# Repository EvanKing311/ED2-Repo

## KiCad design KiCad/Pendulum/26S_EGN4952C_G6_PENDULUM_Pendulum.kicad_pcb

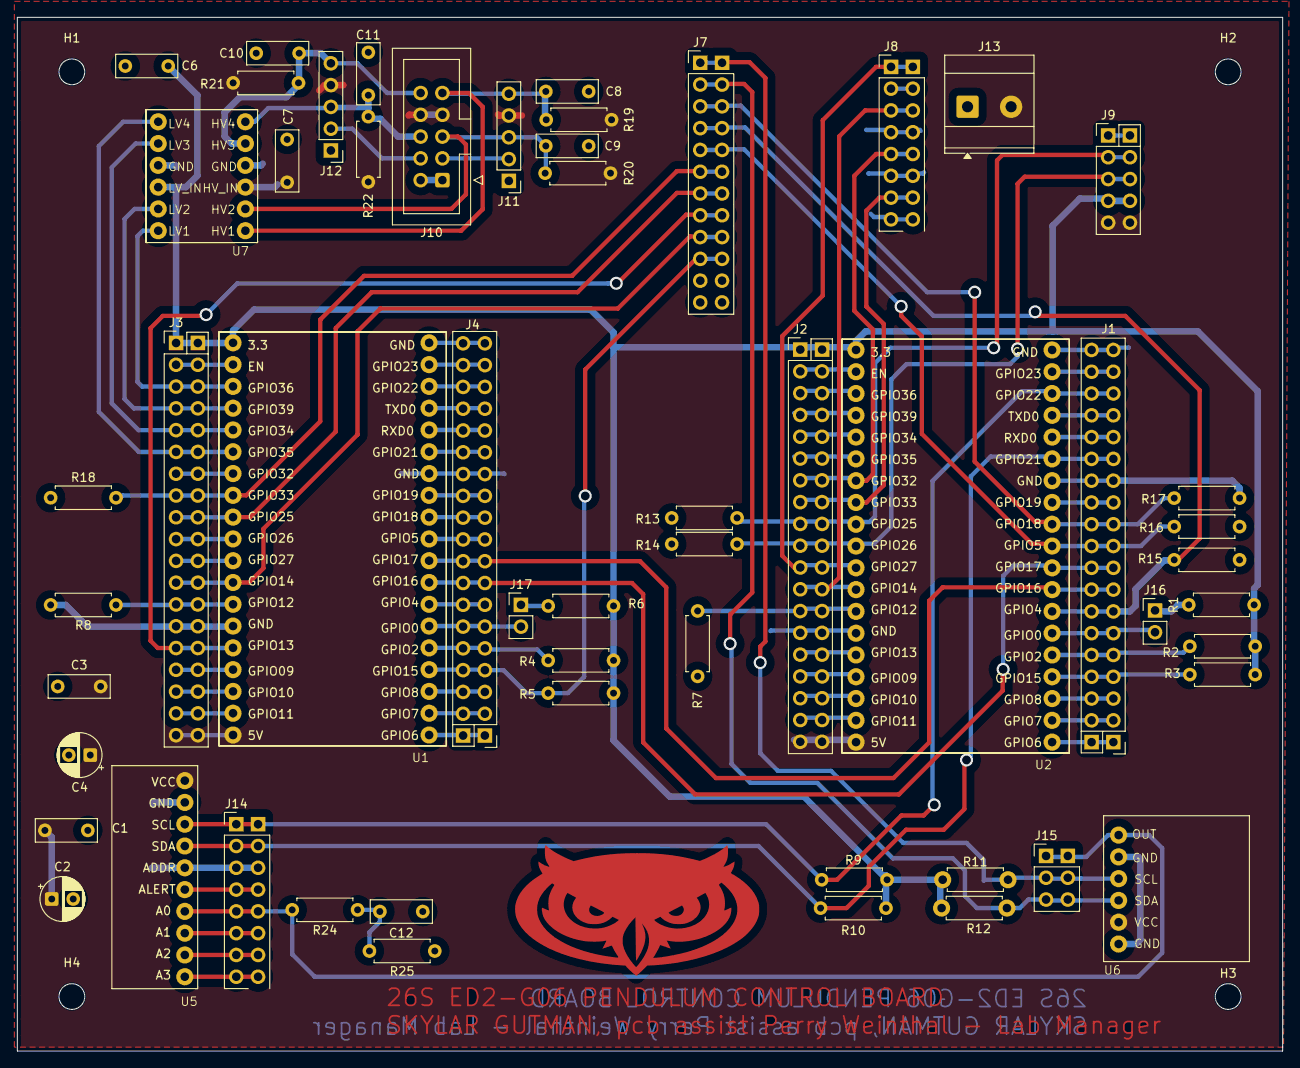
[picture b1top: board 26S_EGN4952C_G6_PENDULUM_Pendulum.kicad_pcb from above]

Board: 2 copper layers, 147.5 x 120.5 mm, 59 parts (0 on the bottom side), 83 nets.

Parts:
C1, C3, C6, C7, C8, C9, C10, C11: 100n; C_Disc_D7.0mm_W2.5mm_P5.00mm
C2, C4: 10u; CP_Radial_D5.0mm_P2.50mm
C12: 10n; C_Disc_D7.0mm_W2.5mm_P5.00mm
H1, H2, H3, H4: MountingHole; MountingHole_3mm
J1: ESP_M_TEST_R; PinHeader_1x19_P2.54mm_Vertical_double
J2: ESP_M_TEST_L; PinHeader_1x19_P2.54mm_Vertical_double
J3, J4: ESP_E_TEST_R; PinHeader_1x19_P2.54mm_Vertical_double
J7: PI_CONN; PinHeader_1x12_P2.54mm_Vertical_Double
J8: SWITCH_CONN; PinHeader_1x08_P2.54mm_Vertical_Double
J9: IBT2_CONN; PinHeader_1x05_P2.54mm_Vertical_Double
J10: ENCODER; IDC-Header_2x05_P2.54mm_Vertical
J11: EN_TEST_ODD; PinHeader_1x05_P2.54mm_Vertical
J12: EN_TEST_EVEN; PinHeader_1x05_P2.54mm_Vertical
J13: POWER; TerminalBlock_Phoenix_MKDS-3-2-5.08_1x02_P5.08mm_Horizontal
J14: ADS_TEST; PinHeader_1x08_P2.54mm_Vertical_Double
J15: MCP_TEST; PinHeader_1x03_P2.54mm_Vertical_Double
J16, J17: OFF=Flash; PinHeader_1x02_P2.54mm_Vertical
R1, R2, R3, R4, R5, R6, R7, R8, R13, R14, R15, R16, R17, R18: 10K; R_Axial_DIN0207_L6.3mm_D2.5mm_P7.62mm_Horizontal
R9, R10, R11, R12, R19, R20, R21, R22: 4.7K; R_Axial_DIN0207_L6.3mm_D2.5mm_P7.62mm_Horizontal
R24: 1K; R_Axial_DIN0207_L6.3mm_D2.5mm_P7.62mm_Horizontal
R25: 100K; R_Axial_DIN0207_L6.3mm_D2.5mm_P7.62mm_Horizontal
U1: ESP#1 ENCODER; NodeMCU_ESP32
U2: ESP#2 MOTOR; NodeMCU_ESP32
U5: ADS1115_MOD; ADS1115
U6: MCP4725; MCP4725_MOD
U7: LEVEL_SHIFTER; LEVEL_SHIFT

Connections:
+3.3V: C6.2, J2.1, J3.1, J9.4, R1.2, R2.2, R3.2, R4.2, R5.2, R6.2, R9.1, R10.1, R11.1, R12.1, U1.1 (3.3v), U2.1 (3.3v), U7.3 (LV_IN)
+5V: C1.2, C2.1, C3.2, C4.1, C7.2, J2.19, J3.19, J9.5, J10.7, J10.8, J11.4, J12.4, J13.2, R19.2, R20.2, R21.2, R22.2, U1.19 (5V), U2.19 (5V), U5.1 (VCC), U6.5 (VCC), U7.10 (HV_IN)
/ESP_SCL: J1.17, J14.1, R9.2, U2.36 (GPIO22), U5.3 (SCL)
/ESP_SDA: J1.14, J14.2, R10.2, U2.33 (GPIO21), U5.4 (SDA)
/M_CH_A: C11.2, J10.6, J12.3, R22.1, U7.7 (HV4)
/M_CH_B: C10.2, J10.10, J12.5, R21.1, U7.8 (HV3)
/M_ENC_A: J3.4, U1.4 (GPIO39), U7.2 (LV2)
/M_ENC_B: J3.3, U1.3 (GPIO36), U7.1 (LV1)
/PI_HOMING: J1.11, J7.3, R17.1, U2.30 (GPIO18)
/PI_SCL: J7.1, J15.2, R11.2, U6.3 (SCL)
/PI_SDA: J7.2, J15.3, R12.2, U6.4 (SDA)
/PI_START: J1.7, J7.4, R15.1, U2.26 (GPIO4)
/PI_STOP: J1.10, J7.5, R16.1, U2.29 (GPIO5)
/P_CH_A: C9.2, J10.5, J11.3, R20.1, U7.11 (HV2)
/P_CH_B: C8.2, J10.9, J11.5, R19.1, U7.12 (HV1)
/P_ENC_A: J3.6, U1.6 (GPIO35), U7.6 (LV4)
/P_ENC_B: J3.5, U1.5 (GPIO34), U7.5 (LV3)
/RESET: J3.8, J7.6, R18.2, U1.8 (GPIO33)
/SPI_CS: J4.4, J7.10, R5.1, U1.23 (GPIO15)
/SPI_M0SI: J3.15, J7.8, U1.15 (GPIO13)
/SPI_MISO: J3.9, J7.7, U1.9 (GPIO25)
/SPI_SCLK: J3.12, J7.9, U1.12 (GPIO14)
GND: C1.1, C2.2, C3.1, C4.2, C6.1, C7.1, C8.1, C9.1, C10.1, C11.1, C12.1, J1.13, J1.19, J2.14, J3.14, J4.13, J4.19, J8.2, J8.4, J8.6, J8.8, J9.1, J10.1, J10.2, J11.1, J12.1, J13.1, J14.3, R7.2, R8.2, R13.2, R14.2, R15.2, R16.2, R17.2, R18.1, R25.1, U1.14 (GND), U1.32 (GND), U1.38 (GND), U2.14 (GND), U2.32 (GND), U2.38 (GND), U5.2 (GND), U5.5 (ADDR), U6.2 (GND), U6.6 (GND), U7.4 (GND), U7.9 (GND)
unnamed: C12.2, R24.1, R25.2
unnamed: J1.1, U2.20 (GPIO6)
unnamed: J1.2, U2.21 (GPIO7)
unnamed: J1.3, U2.22 (GPIO8)
unnamed: J1.4, R3.1, U2.23 (GPIO15)
unnamed: J1.5, R2.1, U2.24 (GPIO2)
unnamed: J1.6, J16.2, U2.25 (GPIO0)
unnamed: J1.8, J4.9, U1.28 (GPIO17), U2.27 (GPIO16)
unnamed: J1.9, J4.8, U1.27 (GPIO16), U2.28 (GPIO17)
unnamed: J1.12, U2.31 (GPIO19)
unnamed: J1.15, U2.34 (GPIO3_RX0)
unnamed: J1.16, U2.35 (GPIO1_TX0)
unnamed: J1.18, U2.37 (GPIO23)
unnamed: J2.2, U2.2 (EN)
unnamed: J2.3, U2.3 (GPIO36)
unnamed: J2.4, U2.4 (GPIO39)
unnamed: J2.5, U2.5 (GPIO34)
unnamed: J2.6, U2.6 (GPIO35)
unnamed: J2.7, J8.5, U2.7 (GPIO32)
unnamed: J2.8, J8.7, U2.8 (GPIO33)
unnamed: J2.9, J9.2, R13.1, U2.9 (GPIO25)
unnamed: J2.10, J9.3, R14.1, U2.10 (GPIO26)
unnamed: J2.11, J8.1, U2.11 (GPIO27)
unnamed: J2.12, J8.3, U2.12 (GPIO14)
unnamed: J2.13, R7.1, U2.13 (GPIO12)
unnamed: J2.15, U2.15 (GPIO13)
unnamed: J2.16, U2.16 (GPIO9)
unnamed: J2.17, U2.17 (GPIO10)
unnamed: J2.18, U2.18 (GPIO11)
unnamed: J3.2, U1.2 (EN)
unnamed: J3.7, U1.7 (GPIO32)
unnamed: J3.10, U1.10 (GPIO26)
unnamed: J3.11, U1.11 (GPIO27)
unnamed: J3.13, R8.1, U1.13 (GPIO12)
unnamed: J3.16, U1.16 (GPIO9)
unnamed: J3.17, U1.17 (GPIO10)
unnamed: J3.18, U1.18 (GPIO11)
unnamed: J4.1, U1.20 (GPIO6)
unnamed: J4.2, U1.21 (GPIO7)
unnamed: J4.3, U1.22 (GPIO8)
unnamed: J4.5, R4.1, U1.24 (GPIO2)
unnamed: J4.7, U1.26 (GPIO4)
unnamed: J4.10, U1.29 (GPIO5)
unnamed: J4.11, U1.30 (GPIO18)
unnamed: J4.12, U1.31 (GPIO19)
unnamed: J4.14, U1.33 (GPIO21)
unnamed: J4.15, U1.34 (GPIO3_RX0)
unnamed: J4.16, U1.35 (GPIO1_TX0)
unnamed: J4.17, U1.36 (GPIO22)
unnamed: J4.18, U1.37 (GPIO23)
unnamed: J10.3, J11.2
unnamed: J10.4, J12.2
unnamed: J14.4, U5.6 (ALERT)
unnamed: J14.5, J15.1, R24.2, U5.7 (A0), U6.1 (OUT)
unnamed: J14.6, U5.8 (A1)
unnamed: J14.7, U5.9 (A2)
unnamed: J14.8, U5.10 (A3)
unnamed: J16.1, R1.1
unnamed: J17.1, R6.1
unnamed: J4.6, J17.2, U1.25 (GPIO0)

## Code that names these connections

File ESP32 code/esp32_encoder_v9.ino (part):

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#define PEND_ENC_B      34

// --- SPI Slave Pins ---
#define SPI_MISO        19
#define SPI_MOSI        23
#define SPI_SCLK        18
#define SPI_CS           5

// --- UART2 Pins (to ESP32 #2) ---
#define UART_TX         17
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
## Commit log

2026-03-06 New Version
2026-04-01 view only, inactivity timer, mqtt updates
2026-04-07 Feedback Pendulum Update to PI
2026-04-14 Live Graphing Changes
2026-04-15 Changes for PI
2026-04-16 nested parameters for CartControl, others can be added (multiple PID)
2026-04-20 Consolidation of PI Models for Pendulum
2026-04-20 2nd Consolidated
2026-04-21 live graphing, readings limit, nested parameters for experiments with multiple PIDs
2026-04-22 Save 4-21-2027
2026-04-22 2026-04-22 Changes
2026-04-24 add remaining experiments, move graph up on the page
2026-04-24 4-24-2026 Update
2026-04-28 2026-04-27 Update
2026-04-29 fix SwingHold Parameters, allow URL to pass user login
2026-05-01 add EStop Button for instructors
2026-05-01 picontrol/Simulink updates 2026/5/1
2026-05-01 Add streaming script for Raspberry Pi camera
    This script streams video from a Raspberry Pi camera to a specified server using ffmpeg.
2026-05-01 esp32 update and simulink files
2026-05-02 mediamtx.yml added
    Add global configuration settings for MediaMTX.
2026-05-02 the ssh tunnel service workaround
2026-05-02 Add systemd service for Pi camera SRT stream
2026-05-02 added kicad files
2026-05-05 added documentation files
2026-05-05 added readme.md
